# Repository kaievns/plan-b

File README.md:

# Plan B

This is a tiny opinionated PCB that has everything packed in one place for
creating split bluetooth keyboards on top of nrf52840 chip and ZMK firmware

Think about it as

- an improved nice!nano clone in a smaller package
- has baked nice!view inside with a slot for LCD
- has baked in RGB controller
- has baked in 6-pin SPI interface for external sensor
- has baked in wiring for 6x6 keyboard matrix via JST connectors
- has baked in power/reset switches for both sides
- high efficiency DC/DC buck converters for all power lines
- heavily fabrication optimised BOM and PCB (est $130 per 5 units at JLCPCB)

All in a tiny 14x42mm package, which is about 8m longer than nice!view shield

## Copyright & License

Everything is released under the terms of the CC BY-SA 4.0 license

© 2025 Kai Evans

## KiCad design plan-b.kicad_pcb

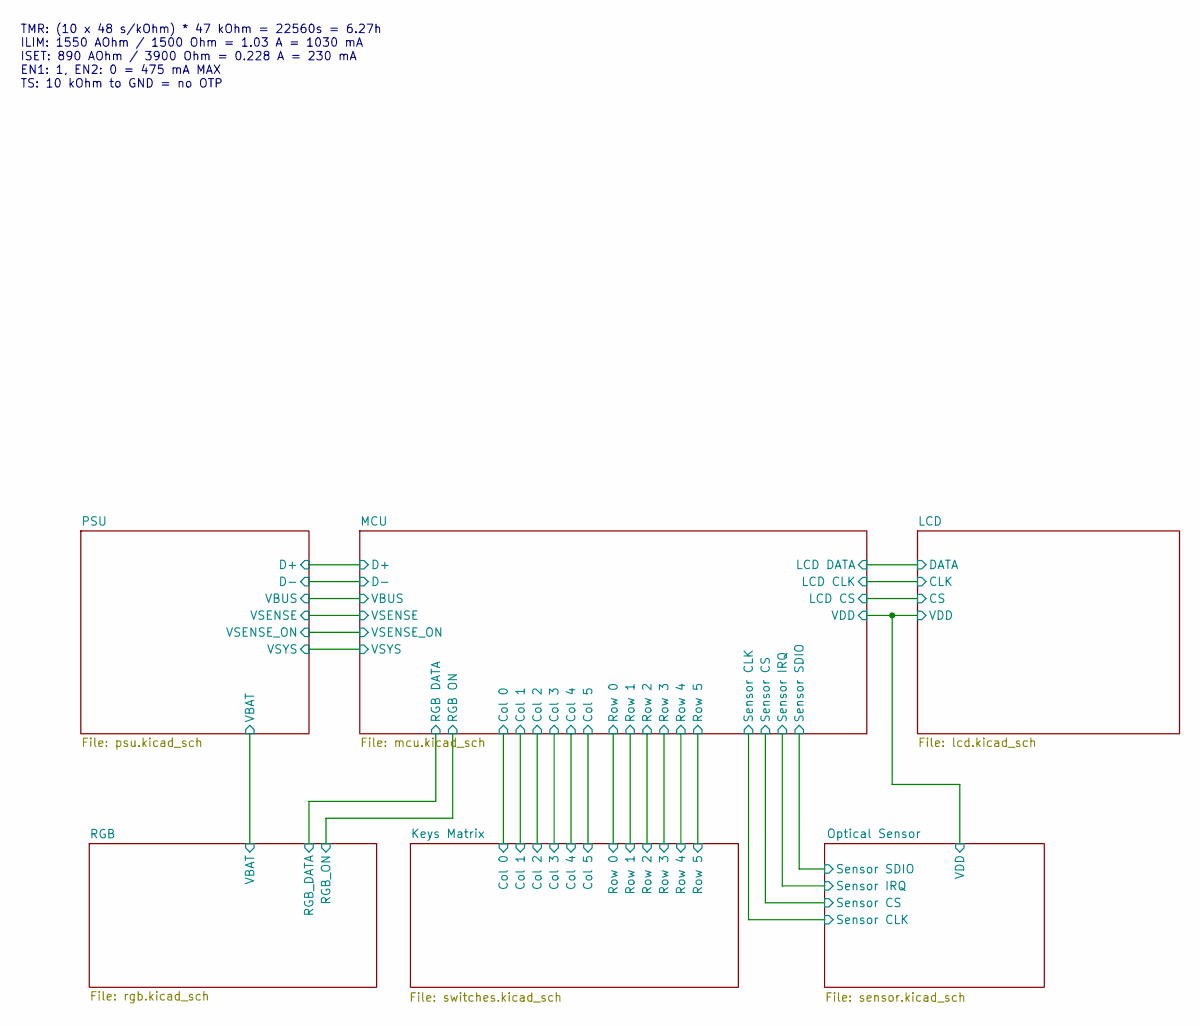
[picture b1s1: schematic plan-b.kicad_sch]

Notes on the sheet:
TMR: (10 x 48 s/kOhm) * 47 kOhm = 22560s = 6.27h ILIM: 1550 AOhm / 1500 Ohm = 1.03 A = 1030 mA ISET: 890 AOhm / 3900 Ohm = 0.228 A = 230 mA EN1: 1, EN2: 0 = 475 mA MAX TS: 10 kOhm to GND = no OTP

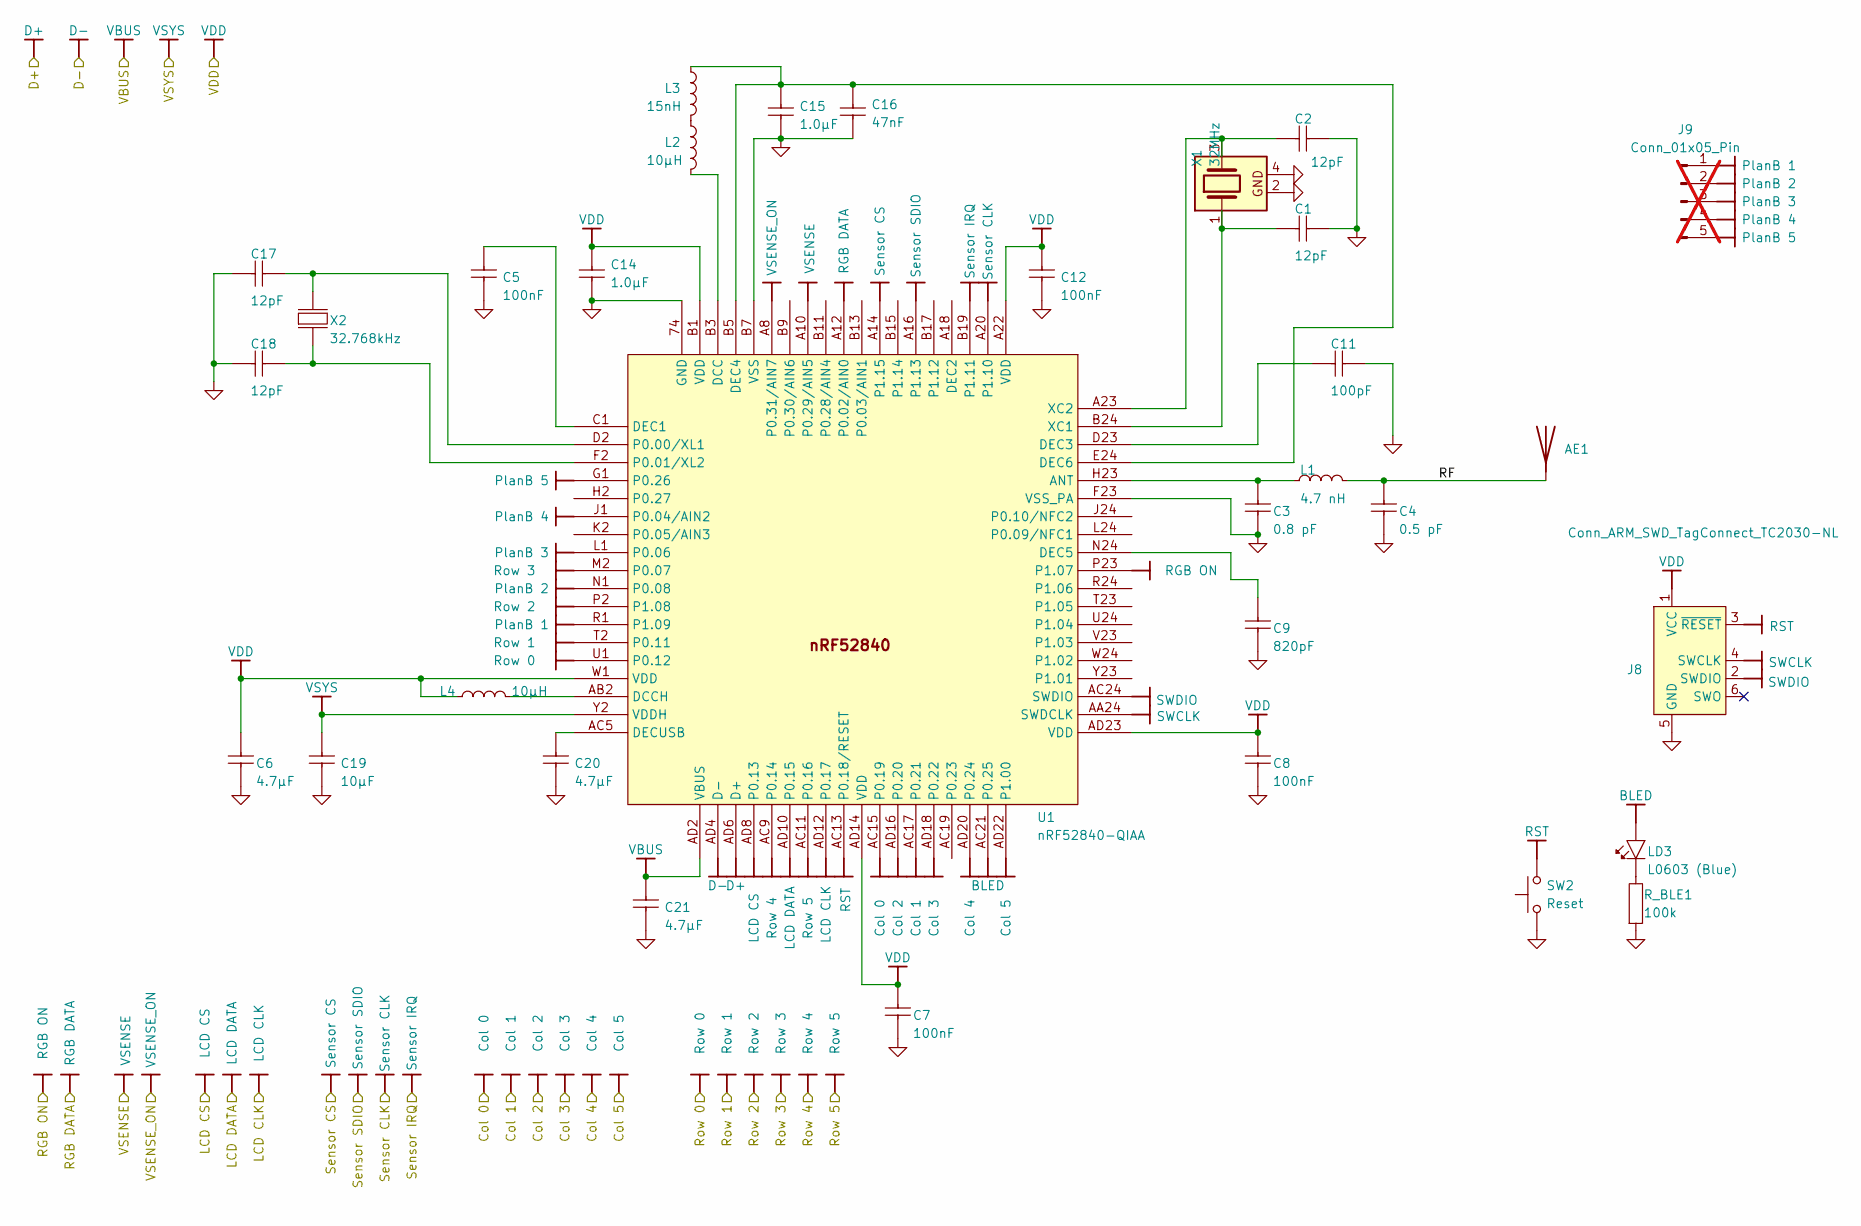
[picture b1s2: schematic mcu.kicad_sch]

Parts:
AE1: ANT2012LL13R2400A; PARTREV 1.3; LCSC C19192917
C1, C2, C17, C18: 12pF; C_0402_1005; PART NUMBER C0402-12p; LCSC C1547
C3: 0.8 pF; C_0402_1005; PART NUMBER C0402-0.8p; LCSC C40459
C4: 0.5 pF; C_0402_1005; PART NUMBER C0402-0.8p; LCSC C76912
C5, C7, C8, C12: 100nF; C_0402_1005; PART NUMBER C0402-100n; LCSC C1525
C6, C20: 4.7µF; C_0603_1608; PART NUMBER C0603-4µ7-6.3V-X7R; LCSC C1624
C9: 820pF; C_0402_1005; PART NUMBER C0402-100n; LCSC C107031
C11: 100pF; C_0402_1005; PART NUMBER C0402-100p; LCSC C1546
C14, C15: 1.0µF; C_0402_1005; PART NUMBER C0603-1µ0; LCSC C52923
C16: 47nF; C_0402_1005; PART NUMBER C0402-47n; LCSC C82219
C19: 10µF; C_0603_1608; PART NUMBER C0603-4µ7-10V-X7S; LCSC C19702
C21: 4.7µF; C_0603_1608; PART NUMBER C0603-4µ7-10V-X7S; LCSC C1624
J8: Conn_ARM_SWD_TagConnect_TC2030-NL; Tag-Connect_TC2030-IDC-NL_2x03_P1.27mm_Vertical
J9: Conn_01x05_Pin; JST_SHL_SM05B-SHLS-TF_1x05-1MP_P1.00mm_Horizontal; not fitted
L1: 4.7 nH; L_0402_1005; PART NUMBER L0402-4n7; LCSC C86065
L2, L4: 10µH; L_0603_1608; PART NUMBER L0603-10µ; LCSC C1035
L3: 15nH; L_0402_1005; PART NUMBER L0402-15n; LCSC C86059
LD3: L0603 (Blue); LED_0603_1608; LCSC C84266
R_BLE1: 100k; R_0402_1005; LCSC C25741
SW2: Reset; SW_SPST_B3U-3000P-B; LCSC C963349
U1: nRF52840-QIAA; Nordic_AQFN-73-1EP_7x7mm_P0.5mm; PART NUMBER nRF52840-QIAA; LCSC C1851953
X1: 32MHz; OSCSC105P160X120X35-4N; PART NUMBER XTAL_SMD2016_32MHz_8pF_General; LCSC C910049
X2: 32.768kHz; XTAL_ECS32761210TR; PART NUMBER XTAL_SMD3215_32.768kHz_9pF_General; LCSC C5682932

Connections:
/MCU/RF: AE1.1 (A), C4.2, L1.2
BLED: LD3.2 (A), U1.AC21 (P0.25)
CLK: U1.AD12 (P0.17); also elsewhere on the board
CS: U1.AD8 (P0.13); also elsewhere on the board
Col 0: U1.AC15 (P0.19); also elsewhere on the board
Col 1: U1.AC17 (P0.21); also elsewhere on the board
Col 2: U1.AD16 (P0.20); also elsewhere on the board
Col 3: U1.AD18 (P0.22); also elsewhere on the board
Col 4: U1.AD20 (P0.24); also elsewhere on the board
Col 5: U1.AD22 (P1.00); also elsewhere on the board
D+: U1.AD6 (D+); also elsewhere on the board
D-: U1.AD4 (D-); also elsewhere on the board
DATA: U1.AD10 (P0.15); also elsewhere on the board
GND: C1.2, C2.2, C3.1, C4.1, C5.2, C6.2, C7.2, C8.2, C9.2, C11.2, C12.2, C14.2, C15.1, C16.2, C17.2, C18.2, C19.2, C20.2, C21.2, J8.5 (GND), R_BLE1.2, SW2.1, U1.74 (GND), U1.B7 (VSS), U1.F23 (VSS_PA), X1.2, X1.4; also elsewhere on the board
unnamed: L2.1, L3.2
unnamed: LD3.1 (C), R_BLE1.1
unnamed: C3.2, L1.1, U1.H23 (ANT)
unnamed: L2.2, U1.B3 (DCC)
unnamed: L4.2, U1.AB2 (DCCH)
unnamed: C5.1, U1.C1 (DEC1)
unnamed: C11.1, U1.D23 (DEC3)
unnamed: C15.2, C16.1, L3.1, U1.B5 (DEC4), U1.E24 (DEC6)
unnamed: C9.1, U1.N24 (DEC5)
unnamed: C20.1, U1.AC5 (DECUSB)
unnamed: C17.1, U1.D2 (P0.00/XL1), X2.1 (inp)
unnamed: C18.1, U1.F2 (P0.01/XL2), X2.2 (out)
unnamed: C1.1, U1.B24 (XC1), X1.1
unnamed: C2.1, U1.A23 (XC2), X1.3
PlanB 1: J9.1, U1.R1 (P1.09)
PlanB 2: J9.2, U1.N1 (P0.08)
PlanB 3: J9.3, U1.L1 (P0.06)
PlanB 4: J9.4, U1.J1 (P0.04/AIN2)
PlanB 5: J9.5, U1.G1 (P0.26)
RGB DATA: U1.A12 (P0.02/AIN0); also elsewhere on the board
RGB ON: U1.P23 (P1.07); also elsewhere on the board
RST: J8.3 (~RESET), SW2.2, U1.AC13 (P0.18/RESET); also elsewhere on the board
Row 0: U1.U1 (P0.12); also elsewhere on the board
Row 1: U1.T2 (P0.11); also elsewhere on the board
Row 2: U1.P2 (P1.08); also elsewhere on the board
Row 3: U1.M2 (P0.07); also elsewhere on the board
Row 4: U1.AC9 (P0.14); also elsewhere on the board
Row 5: U1.AC11 (P0.16); also elsewhere on the board
SWCLK: J8.4 (SWCLK), U1.AA24 (SWDCLK)
SWDIO: J8.2 (SWDIO), U1.AC24 (SWDIO)
Sensor CLK: U1.A20 (P1.10); also elsewhere on the board
Sensor CS: U1.A14 (P1.15); also elsewhere on the board
Sensor IRQ: U1.B19 (P1.11); also elsewhere on the board
Sensor SDIO: U1.A16 (P1.13); also elsewhere on the board
VBUS: C21.1, U1.AD2 (VBUS); also elsewhere on the board
VDD: C6.1, C7.1, C8.1, C12.1, C14.1, J8.1 (VCC), L4.1, U1.A22 (VDD), U1.AD14 (VDD), U1.AD23 (VDD), U1.B1 (VDD), U1.W1 (VDD); also elsewhere on the board
VSENSE: U1.A10 (P0.29/AIN5); also elsewhere on the board
VSENSE_ON: U1.A8 (P0.31/AIN7); also elsewhere on the board
VSYS: C19.1, U1.Y2 (VDDH); also elsewhere on the board

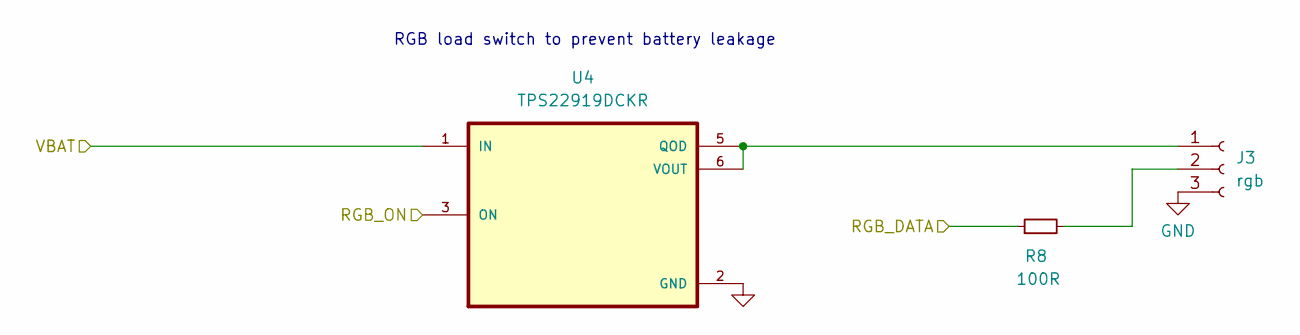
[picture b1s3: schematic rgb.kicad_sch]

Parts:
J3: rgb; JST_SH_SM03B-SRSS-TB_1x03-1MP_P1.00mm_Horizontal; LCSC C160403
R8: 100R; R_0402_1005; LCSC C25076
U4: TPS22919DCKR; SOT-363_SC-70-6; LCSC C2149796

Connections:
GND: J3.3, U4.2 (GND); also elsewhere on the board
unnamed: J3.1, U4.5 (QOD), U4.6 (VOUT)
unnamed: J3.2, R8.2
RGB DATA: R8.1; also elsewhere on the board
RGB ON: U4.3 (ON); also elsewhere on the board
VBAT: U4.1 (IN); also elsewhere on the board

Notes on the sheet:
RGB load switch to prevent battery leakage

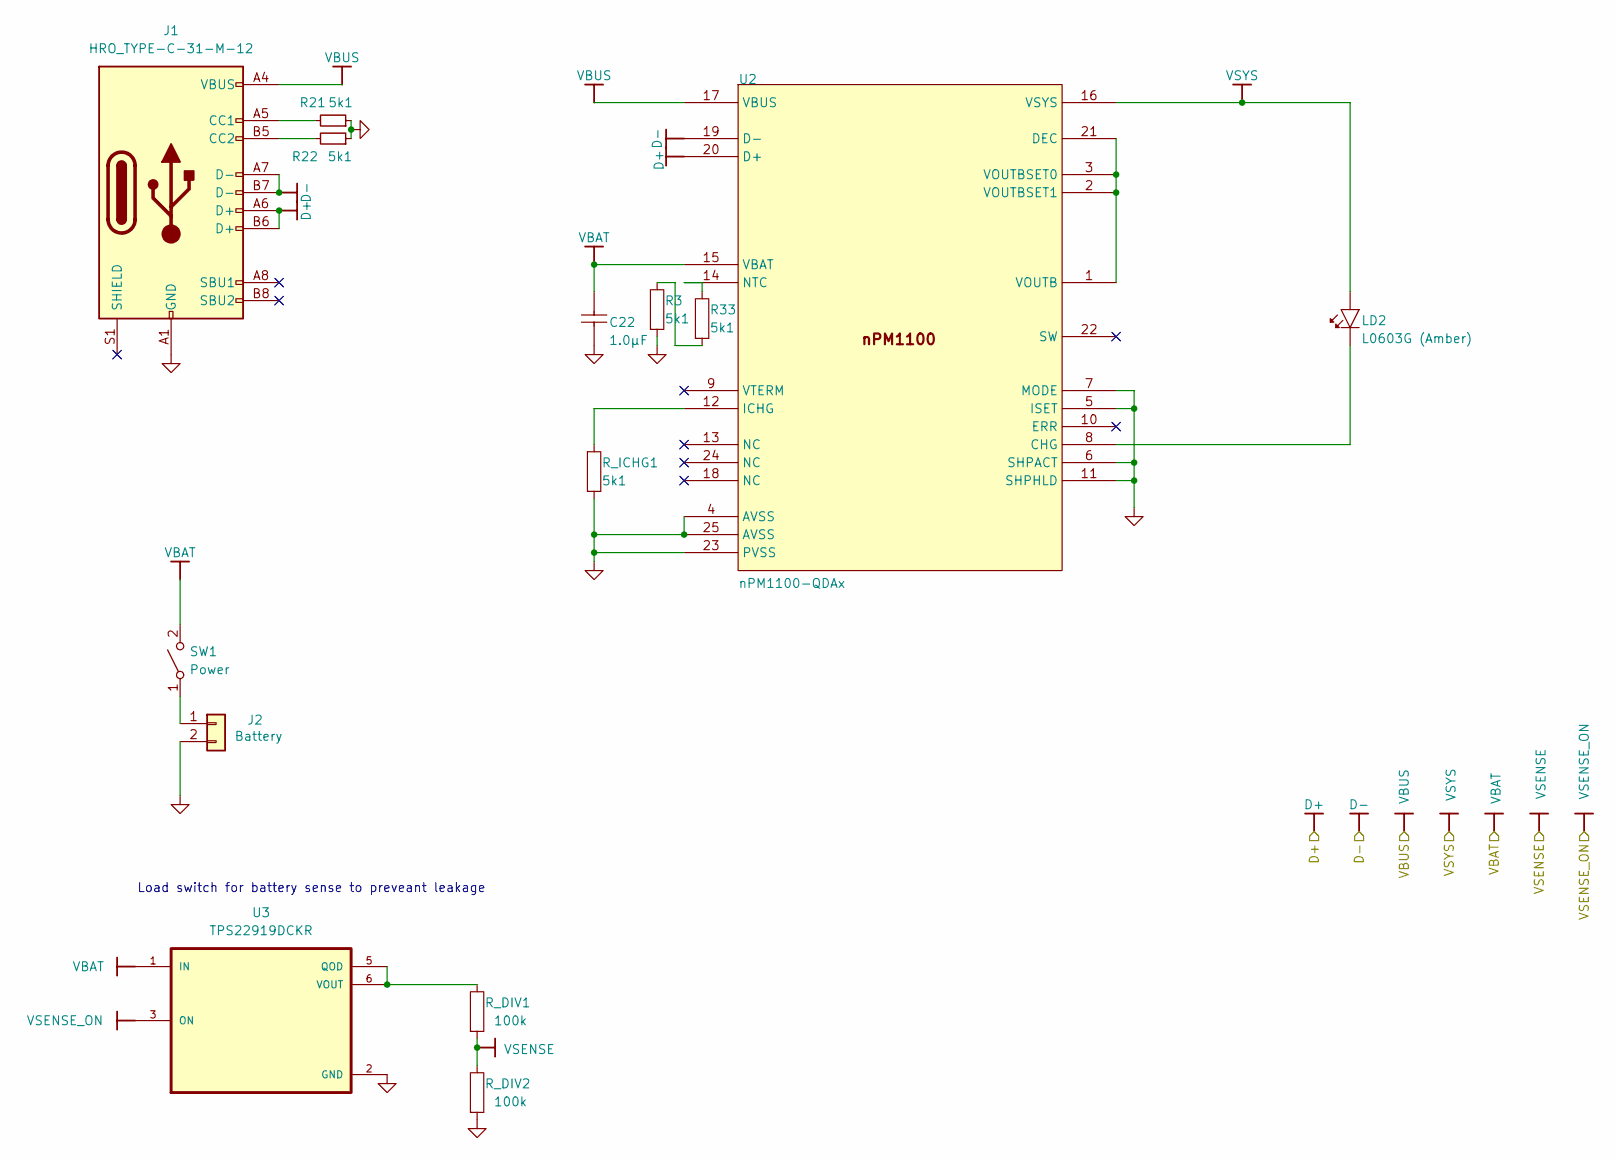
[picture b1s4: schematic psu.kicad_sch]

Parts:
C22: 1.0µF; C_0402_1005; LCSC C52923
J1: HRO_TYPE-C-31-M-12; USB_C_Receptacle_HRO_TYPE-C-31-M-12; LCSC C165948
J2: Battery; JST_SH_SM02B-SRSS-TB_1x02-1MP_P1.00mm_Horizontal; LCSC C160402
LD2: L0603G (Amber); LED_0603_1608; LCSC C84269
R3, R21, R22, R33: 5k1; R_0402_1005; LCSC C25905
R_DIV1, R_DIV2: 100k; R_0402_1005; LCSC C25741
R_ICHG1: 5k1; R_0402_1005; LCSC C25905
SW1: Power; Switch_MSK12C02; LCSC C431540
U2: nPM1100-QDAx; QFN-24-1EP_4x4mm_P0.5mm_EP2.6x2.6mm_ThermalVias; PART NUMBER nRF52840-QIAA; LCSC C5816773
U3: TPS22919DCKR; SOT-363_SC-70-6; LCSC C2149796

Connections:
D+: J1.A6 (D+), J1.B6 (D+), U2.20 (D+); also elsewhere on the board
D-: J1.A7 (D-), J1.B7 (D-), U2.19 (D-); also elsewhere on the board
GND: C22.1, J1.A1 (GND), J1.A12 (GND), J1.B1 (GND), J1.B12 (GND), J2.2, R3.2, R21.1, R22.1, R_DIV2.2, R_ICHG1.1, U2.4 (AVSS), U2.5 (ISET), U2.6 (SHPACT), U2.7 (MODE), U2.11 (SHPHLD), U2.23 (PVSS), U2.25 (AVSS), U3.2 (GND); also elsewhere on the board
unnamed: J1.A5 (CC1), R21.2
unnamed: J1.B5 (CC2), R22.2
unnamed 17: J2.1, SW1.1 (A); also elsewhere on the board
unnamed: LD2.1 (C), U2.8 (CHG)
unnamed: R3.1, R33.2
unnamed: U2.1 (VOUTB), U2.2 (VOUTBSET1), U2.3 (VOUTBSET0), U2.21 (DEC)
unnamed: R_ICHG1.2, U2.12 (ICHG)
unnamed: R33.1, U2.14 (NTC)
unnamed: R_DIV1.1, U3.5 (QOD), U3.6 (VOUT)
VBAT: C22.2, SW1.2 (B), U2.15 (VBAT), U3.1 (IN); also elsewhere on the board
VBUS: J1.A4 (VBUS), J1.A9 (VBUS), J1.B4 (VBUS), J1.B9 (VBUS), U2.17 (VBUS); also elsewhere on the board
VSENSE: R_DIV1.2, R_DIV2.1; also elsewhere on the board
VSENSE_ON: U3.3 (ON); also elsewhere on the board
VSYS: LD2.2 (A), U2.16 (VSYS); also elsewhere on the board

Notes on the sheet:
Load switch for battery sense to preveant leakage

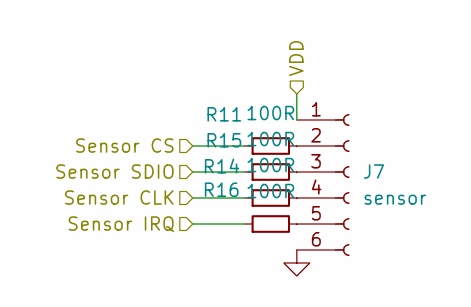
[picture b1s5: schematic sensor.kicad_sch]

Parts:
J7: sensor; JST_SH_SM06B-SRSS-TB_1x06-1MP_P1.00mm_Horizontal; LCSC C160405
R11, R14, R15, R16: 100R; R_0402_1005; LCSC C25076

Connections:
GND: J7.6; also elsewhere on the board
unnamed: J7.2, R11.2
unnamed: J7.3, R14.2
unnamed: J7.4, R15.2
unnamed: J7.5, R16.2
Sensor CLK: R15.1; also elsewhere on the board
Sensor CS: R11.1; also elsewhere on the board
Sensor IRQ: R16.1; also elsewhere on the board
Sensor SDIO: R14.1; also elsewhere on the board
VDD: J7.1; also elsewhere on the board

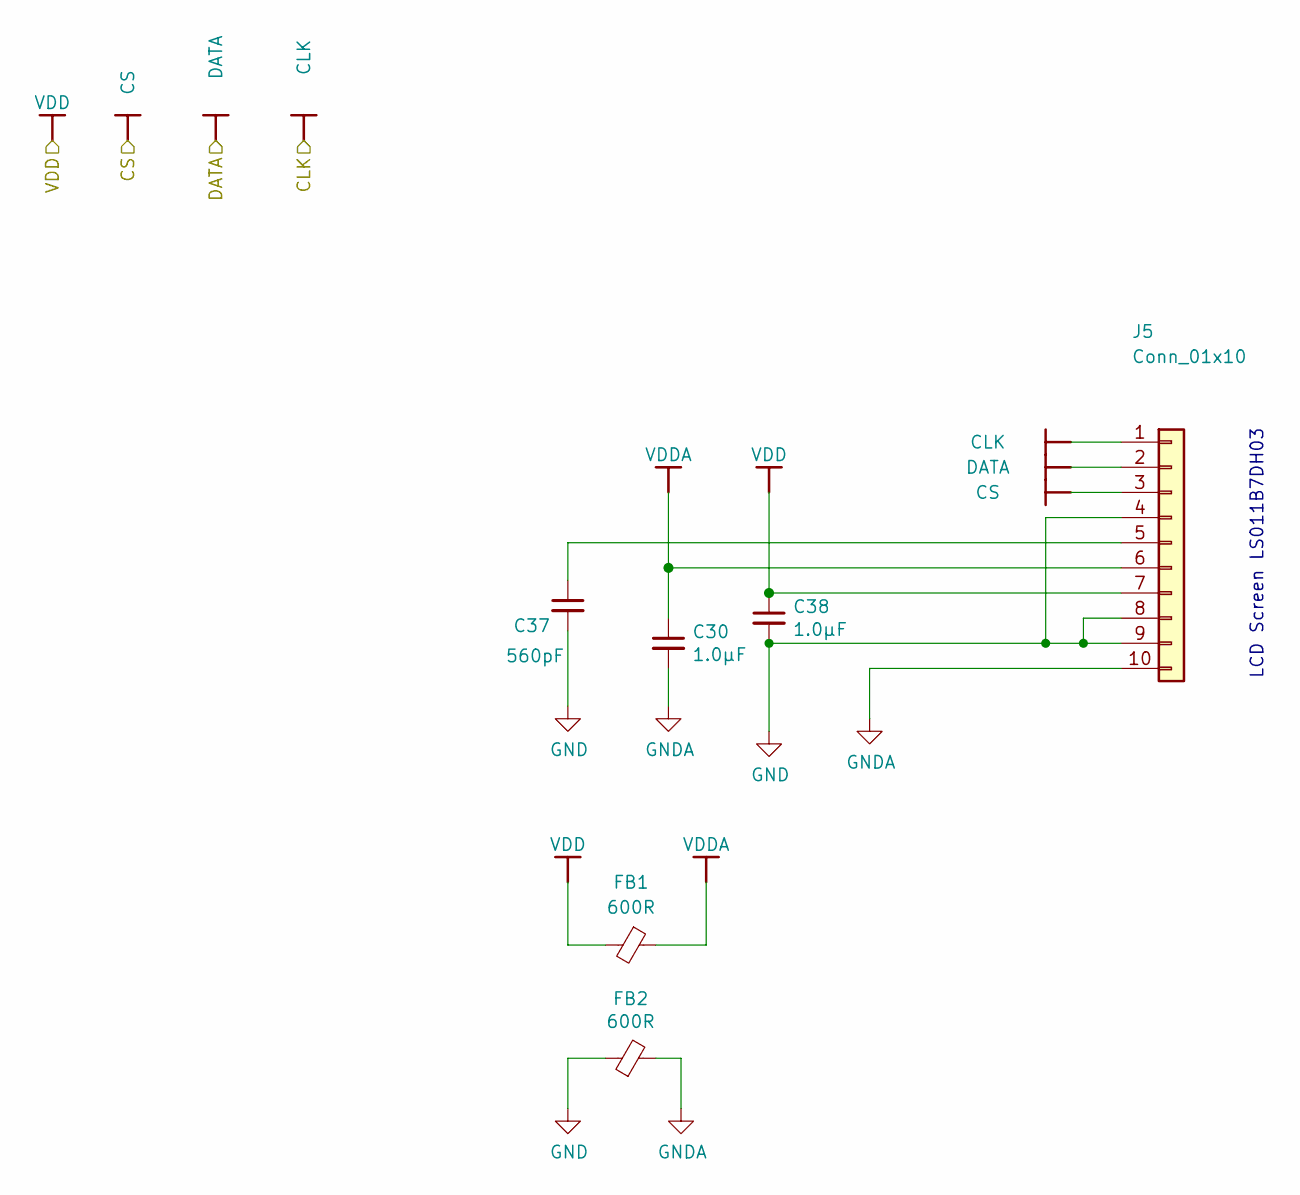
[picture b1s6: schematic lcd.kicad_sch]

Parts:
C30, C38: 1.0µF; C_0402_1005; LCSC C52923
C37: 560pF; C_0402_1005; LCSC C1539
FB1, FB2: 600R; F_0603_1608; LCSC C1002
J5: Conn_01x10; CONN10x1_FH34SRJ-10S-0.5SH50_HIR; LCSC C324723

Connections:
CLK: J5.1; also elsewhere on the board
CS: J5.3; also elsewhere on the board
DATA: J5.2; also elsewhere on the board
GND: C37.2, C38.2, FB2.1, J5.4, J5.8, J5.9; also elsewhere on the board
GNDA: C30.2, FB2.2, J5.10
unnamed: C37.1, J5.5
VDD: C38.1, FB1.2, J5.7; also elsewhere on the board
VDDA: C30.1, FB1.1, J5.6

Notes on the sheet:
LCD Screen LS011B7DH03

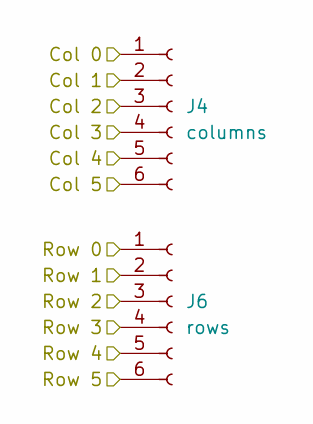
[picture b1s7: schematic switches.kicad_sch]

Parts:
J4: columns; JST_SH_SM06B-SRSS-TB_1x06-1MP_P1.00mm_Horizontal; LCSC C160405
J6: rows; JST_SH_SM06B-SRSS-TB_1x06-1MP_P1.00mm_Horizontal; LCSC C160405

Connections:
Col 0: J4.1; also elsewhere on the board
Col 1: J4.2; also elsewhere on the board
Col 2: J4.3; also elsewhere on the board
Col 3: J4.4; also elsewhere on the board
Col 4: J4.5; also elsewhere on the board
Col 5: J4.6; also elsewhere on the board
Row 0: J6.1; also elsewhere on the board
Row 1: J6.2; also elsewhere on the board
Row 2: J6.3; also elsewhere on the board
Row 3: J6.4; also elsewhere on the board
Row 4: J6.5; also elsewhere on the board
Row 5: J6.6; also elsewhere on the board

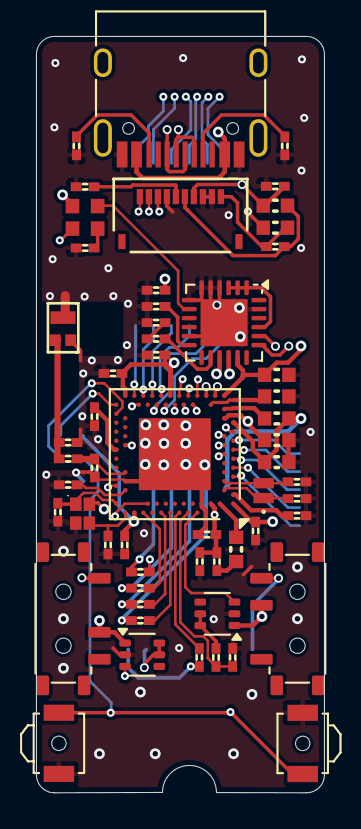
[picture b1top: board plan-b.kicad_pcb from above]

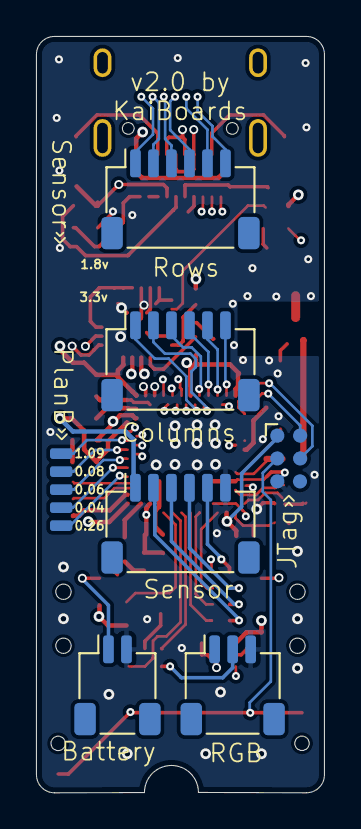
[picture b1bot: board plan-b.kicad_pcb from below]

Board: 4 copper layers, 16.0 x 42.0 mm, 64 parts (7 on the bottom side), 72 nets.

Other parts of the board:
SW1#2: Power; Switch_MSK12C02
SW2#2: Reset; SW_SPST_B3U-3000P-B

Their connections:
GND: SW2#2.1; also elsewhere on the board
unnamed 17: SW1#2.1 (A); also elsewhere on the board
RST: SW2#2.2; also elsewhere on the board
VBAT: SW1#2.2 (B); also elsewhere on the board

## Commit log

2024-08-05 Initial setup
2024-08-07 Initial PCB layout
2024-08-20 Spit and polish
2024-08-25 Adding the left/right hand split
2024-08-26 Creating the reusable key pad
2024-08-29 Final touches for the mobos
2024-08-29 Rewiring the trackball sensor PCB
2024-09-17 Swapping out some components
2024-09-17 Reconnecting all the components on PCB again
2025-01-18 Splitting the KiCAD project into thre independent PCBs
2025-03-28 Resetting the mobo stack to 4 layers mirrorable
2025-03-29 Reworking the mobo into a reversible panel
2025-03-29 Reworking the keypad PCB
2025-09-24 Dumping everything i need into the combined schematic
2025-09-27 Cleaning up the schematics
2025-09-27 Resetting the PCB
2025-09-27 Replacing the through holes with JST-SH connectors
2025-10-07 Adding connectors 3d files
2025-10-11 Assigning all the perifery pins
2025-10-11 Groupping around the PCB components
2025-10-12 Loosely optimising the groups components placement
2025-10-12 Groupping the groups into a workable arrangement
2025-10-12 Sub-compacting the components to their target dimensions
2025-10-12 Partially wiring the bottom half
2025-11-07 Importing reference schematics for nrf52840 and npm1100 chips and renaming the project
2025-11-07 Re-shuffling the schematics across sub-sheets
2025-11-07 Copying over the reference PCB stacks
2025-11-08 Tidying up the mess a little bit
2025-11-09 Re-importing some key components
2025-11-09 Adding the antennae
2025-11-09 Removing the NFC1/2 connectors
2025-11-09 Cleaning up the PSU schematics
2025-11-10 Cleaning up the schematics a bit more
2025-11-11 Updating schematics/pcb to match the labels
2025-11-12 Cleaning up some space on the PCB
2025-11-12 Reseting all the extra components sizes
2025-11-12 Dissolving and re-packaging the PSU block
2025-11-12 Unshielding the main block
2025-11-12 Swapping the crystals for smaller ones
2025-11-13 Dialing in the physical package
2025-11-13 Putting all the components in their rough places
2025-11-14 Backporting footprints from the PCB back to schematic
2025-11-14 Fixes and space optimisations
2025-11-15 Loosely attaching pins to prefiery
2025-11-15 More routing
2025-11-15 Connecting most of the other components
2025-11-16 Connecting remaining power lines
2025-11-16 Adding the J-tag connector for the programmer
2025-11-16 Adding the solid ground fill
2025-11-17 Adding the Plan B pins
2025-11-17 Re-organising the schematics sheets a bit
2025-11-18 Reworking the RGB power section
2025-11-19 Moving the RGB feed capacitor
2025-11-23 Removing the RGB level shifter
2025-11-23 Renaming the project and throwing a read-me
2025-11-25 Reworking the PSU schematic to QDA package, adding DC/DC 1.8v source for optical sensor, and load switch for the battery sensor to prevent leakage
2025-11-25 Swapping the load switches from WLSP to WSON-6 packages
2025-11-25 Reworking the MCU schematics sheet into QIAA package
2025-11-27 Dumping the reference layouts into the PCB
2025-11-28 Adding some basic libarary components
2025-11-29 Cleaning up more components
2025-11-29 Relinking the schematics and the PCB again
2025-11-29 Setting up the RF/Antenna setup
2025-11-29 Tidying up the PSU block
2025-11-29 Switching to smaller crystalls
2025-11-29 Sorting out the remaining components footprints and rough positioning
2025-11-30 Cleaning up the LCD schematics
2025-11-30 Roughly aligning back and front
2025-11-30 Optimising the RF side
2025-12-01 Re-working the PCB cutouts to 16x42mm dimensions and realigning switches and connectors at the back
2025-12-01 Trying the 18x42mm form factor
2025-12-01 Moving the main block in place
2025-12-02 Re-linking the PCB properties back to the schematics
2025-12-04 Compacting the right side of the PCB
2025-12-05 Reworking the PSU block and squeeshing everything into 16x42mm space
2025-12-05 Cleaning up the sensor signals routing
2025-12-05 Wiring up the load swiches side of the PCB
2025-12-06 Sorting out most of the powerlines
2025-12-06 Sorting out other pads and sensor voltage jumper
2025-12-06 Wiring the columns socket
2025-12-06 Swapping rows connector to the same 6 pins as columns
2025-12-07 Wiring the rows connector to the MCU
2025-12-07 Connecting the status LEDs
2025-12-07 Sorting out the GND fills
2025-12-08 Optimising for BOM and placements cost reduction
2025-12-08 Further optimising the BOM and adding JLCPCB specific part numbers
2025-12-09 Updating the readme
2025-12-10 Removing the 1.8v power supply option
